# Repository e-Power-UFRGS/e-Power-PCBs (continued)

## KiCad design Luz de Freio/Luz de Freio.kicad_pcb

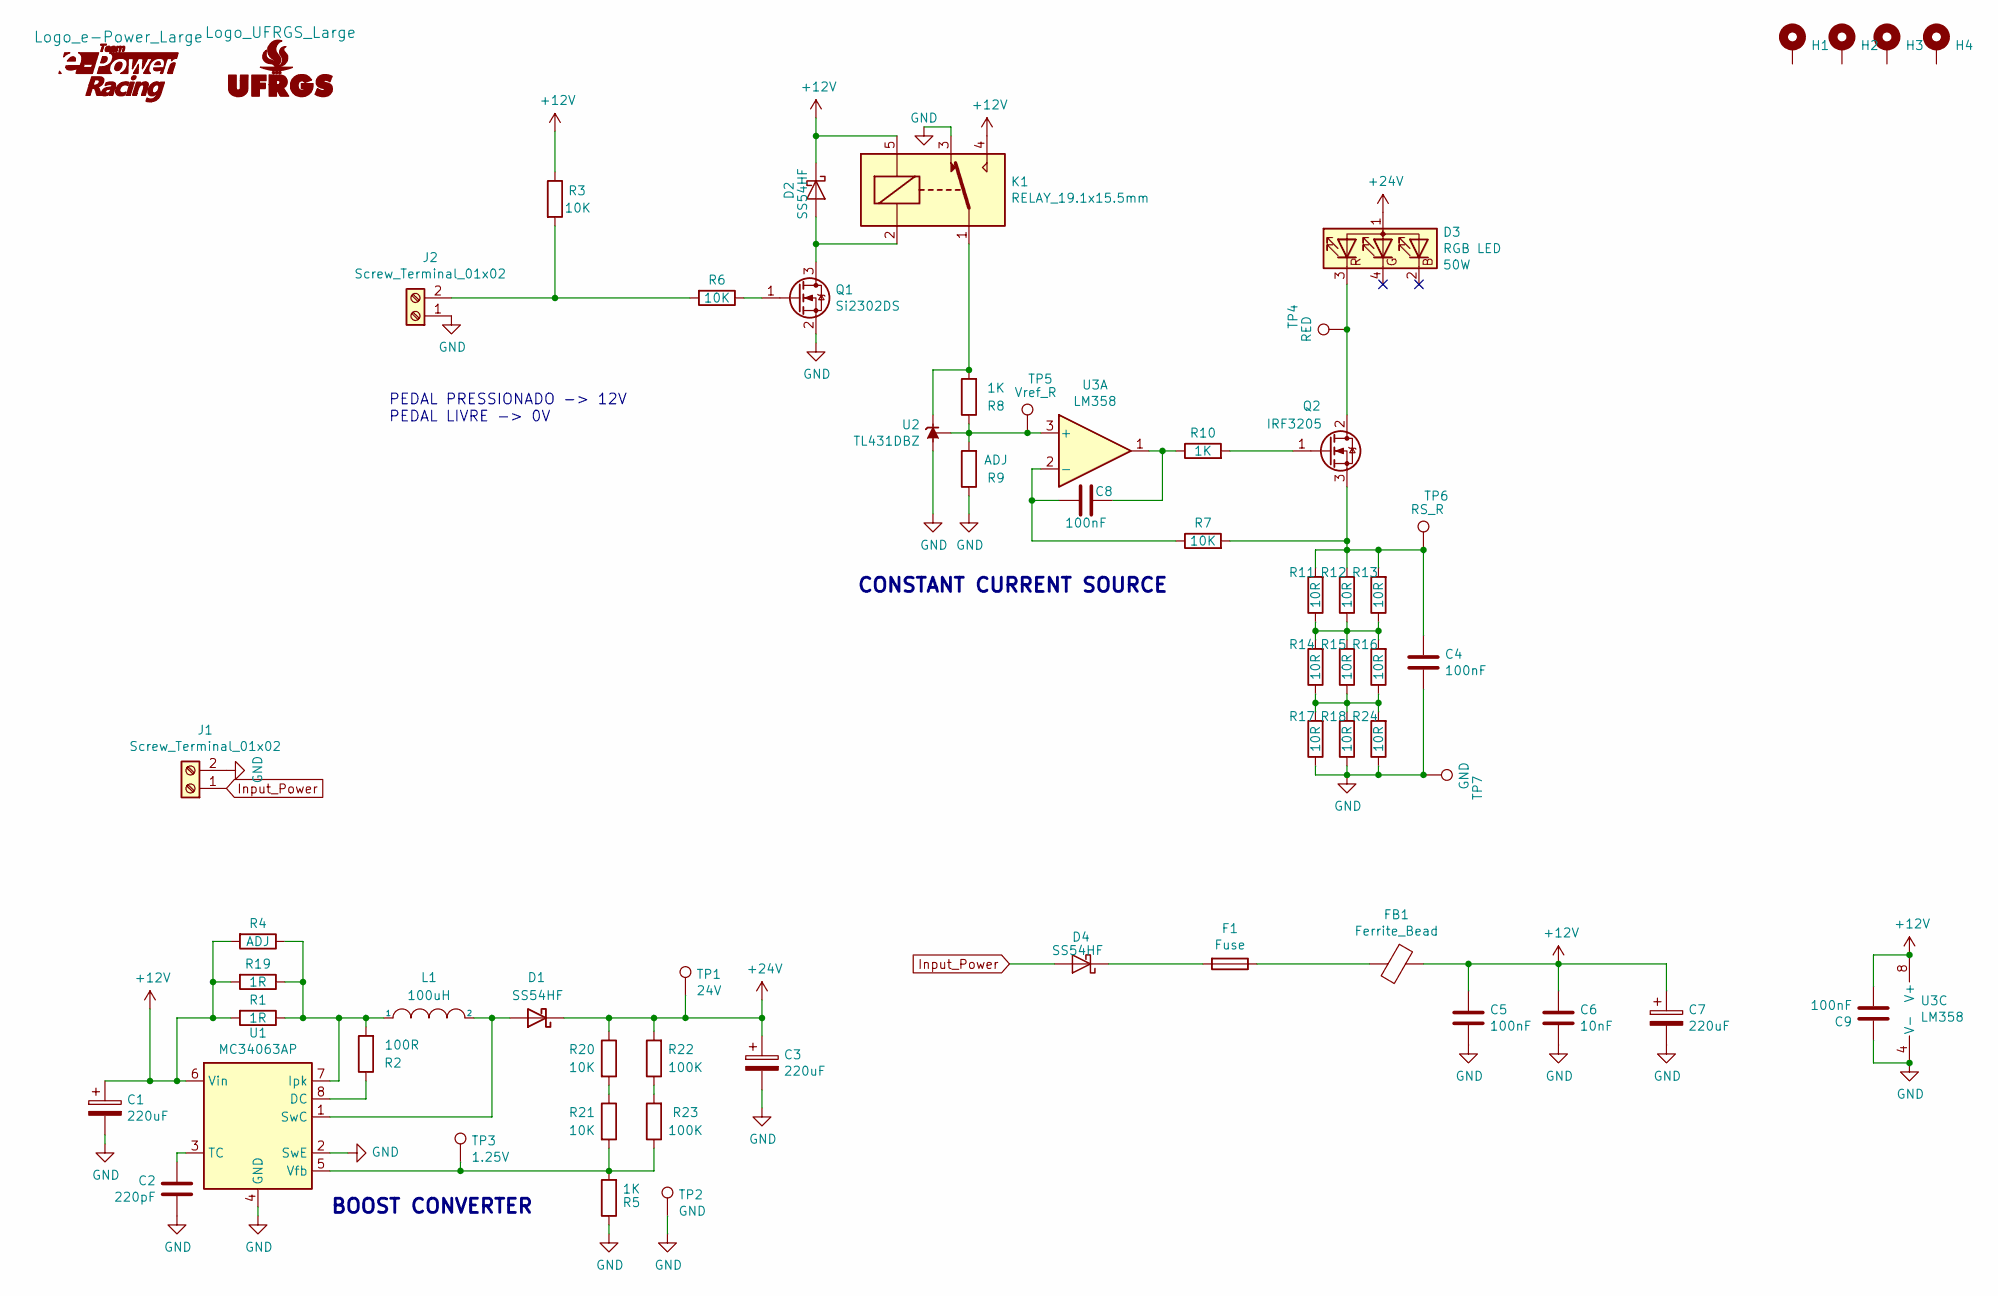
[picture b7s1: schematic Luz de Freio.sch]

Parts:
C1, C3: 220uF; CP_Elec_10x10; Voltage 16V
C2: 220pF; C_0805_2012Metric_Pad1.15x1.40mm_HandSolder
C4, C5, C9: 100nF; C_0805_2012Metric_Pad1.15x1.40mm_HandSolder
C6: 10nF; C_0805_2012Metric_Pad1.15x1.40mm_HandSolder
C7: 220uF; CP_Elec_10x10
C8: 100nF; C_0805_2012Metric
D1, D2, D4: SS54HF; DO-214AC
D3: RGB LED; TerminalBlock_Phoenix_MKDS-1,5-2_1x02_P5.08mm_Horizontal
F1: Fuse; FUSE_1206_3216Metric
FB1: Ferrite_Bead; FB_0805_2012Metric
G1: Logo_UFRGS_Large; Logo_UFRGS_14.7x8.0mm_SilkS
G2: Logo_e-Power_Large; Logo_e-Power_16.5x8.0mm_SilkS
H1, H2, H3, H4: MountingHole_Pad; MountingHole_3.2mm_M3_Pad_Via
J1, J2: Screw_Terminal_01x02; TerminalBlock_Phoenix_MKDS-1,5-2_1x02_P5.08mm_Horizontal
K1: RELAY_19.1x15.5mm; Relay_SPDT_SANYOU_SRD
L1: 100uH; L_12x12mm_H6mm
Q1: Si2302DS; SOT-23
Q2: IRF3205; TO-220-3_Horizontal_TabDown
R1, R19: 1R; R_0805_2012Metric
R2: 100R; R_0805_2012Metric
R3, R6, R7: 10K; R_0805_2012Metric_Pad1.15x1.40mm_HandSolder
R4: ADJ; R_0805_2012Metric
R5: 1K; R_0805_2012Metric
R8, R10: 1K; R_0805_2012Metric_Pad1.15x1.40mm_HandSolder
R9: ADJ; R_0805_2012Metric_Pad1.15x1.40mm_HandSolder
R11, R12, R13, R14, R15, R16, R17, R18, R24: 10R; R_0805_2012Metric_Pad1.15x1.40mm_HandSolder
R20, R21: 10K; R_0805_2012Metric
R22, R23: 100K; R_0805_2012Metric
TP1: 24V; TestPoint_Pad_D1.0mm
TP2, TP7: GND; TestPoint_Pad_D1.0mm
TP3: 1.25V; TestPoint_Pad_D1.0mm
TP4: RED; TestPoint_Pad_D1.0mm
TP5: Vref_R; TestPoint_Pad_D1.0mm
TP6: RS_R; TestPoint_Pad_D1.0mm
U1: MC34063AP; SOIC-8_3.9x4.9mm_P1.27mm
U2: TL431DBZ; SOT-23
U3: LM358; SOIC-8_3.9x4.9mm_P1.27mm

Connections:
+12V: C1.1, C5.1, C6.1, C7.1, C9.1, D2.1 (K), FB1.1, K1.4, K1.5, R1.2, R3.1, R4.2, R19.2, U1.6 (Vin), U3.8 (V+)
+24V: C3.1, D1.1 (K), D3.1 (A), R20.1, R22.2, TP1.1
GND: C1.2, C2.1, C3.2, C4.1, C5.2, C6.2, C7.2, C9.2, J1.2, J2.1, K1.3, Q1.2 (S), R5.1, R9.1, R17.1, R18.1, R24.1, TP2.1, TP7.1, U1.2 (SwE), U1.4 (GND), U2.3 (A), U3.4 (V-)
Input_Power: D4.2 (A), J1.1
unnamed: C2.2, U1.3 (TC)
unnamed: C4.2, Q2.3 (S), R7.2, R11.2, R12.2, R13.2, TP6.1
unnamed: C8.1, R10.1, U3.1
unnamed: C8.2, R7.1, U3.2 (-)
unnamed: D1.2 (A), L1.2, U1.1 (SwC)
unnamed: D2.2 (A), K1.2, Q1.3 (D)
unnamed: D3.3 (RK), Q2.2 (D), TP4.1
unnamed: D4.1 (K), F1.2
unnamed: F1.1, FB1.2
unnamed: J2.2, R3.2, R6.2
unnamed: K1.1, R8.2, U2.1 (K)
unnamed: L1.1, R1.1, R2.2, R4.1, R19.1, U1.7 (Ipk)
unnamed: Q1.1 (G), R6.1
unnamed: Q2.1 (G), R10.2
unnamed: R2.1, U1.8 (DC)
unnamed: R8.1, R9.2, TP5.1, U2.2 (REF), U3.3 (+)
unnamed: R11.1, R12.1, R13.1, R14.2, R15.2, R16.2
unnamed: R14.1, R15.1, R16.1, R17.2, R18.2, R24.2
unnamed: R20.2, R21.1
unnamed: R5.2, R21.2, R23.1, TP3.1, U1.5 (Vfb)
unnamed: R22.1, R23.2

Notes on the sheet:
CONSTANT CURRENT SOURCE
BOOST CONVERTER
PEDAL PRESSIONADO -> 12V PEDAL LIVRE -> 0V

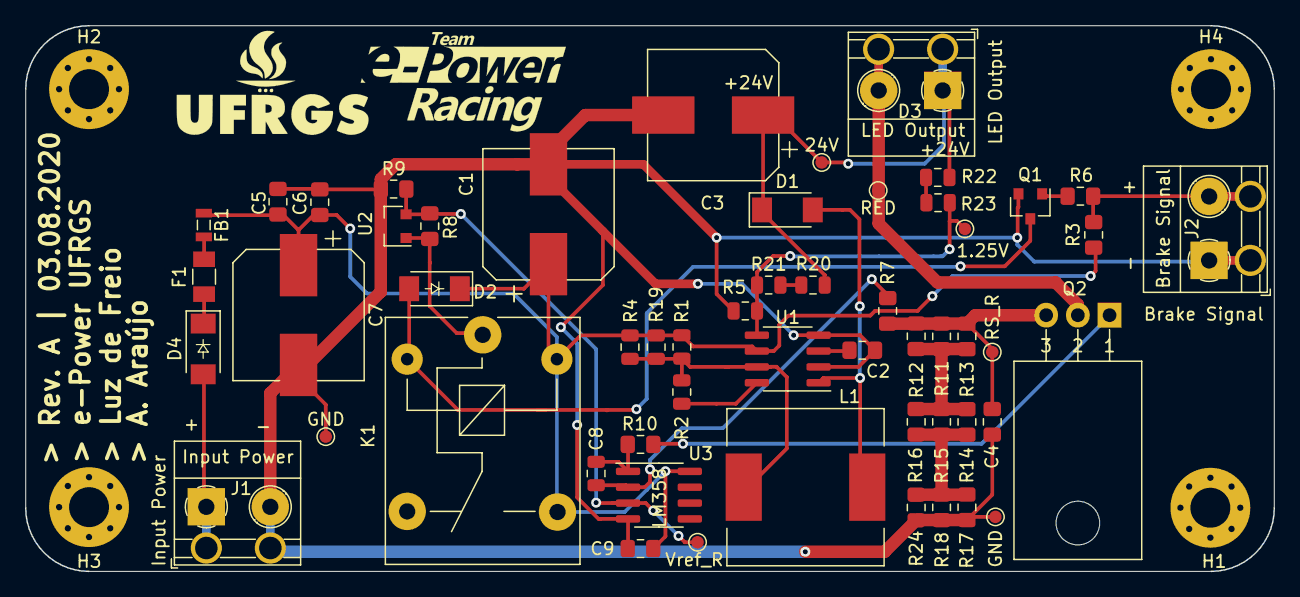
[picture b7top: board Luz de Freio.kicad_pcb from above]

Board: 2 copper layers, 100.1 x 43.7 mm, 61 parts (0 on the bottom side), 25 nets.

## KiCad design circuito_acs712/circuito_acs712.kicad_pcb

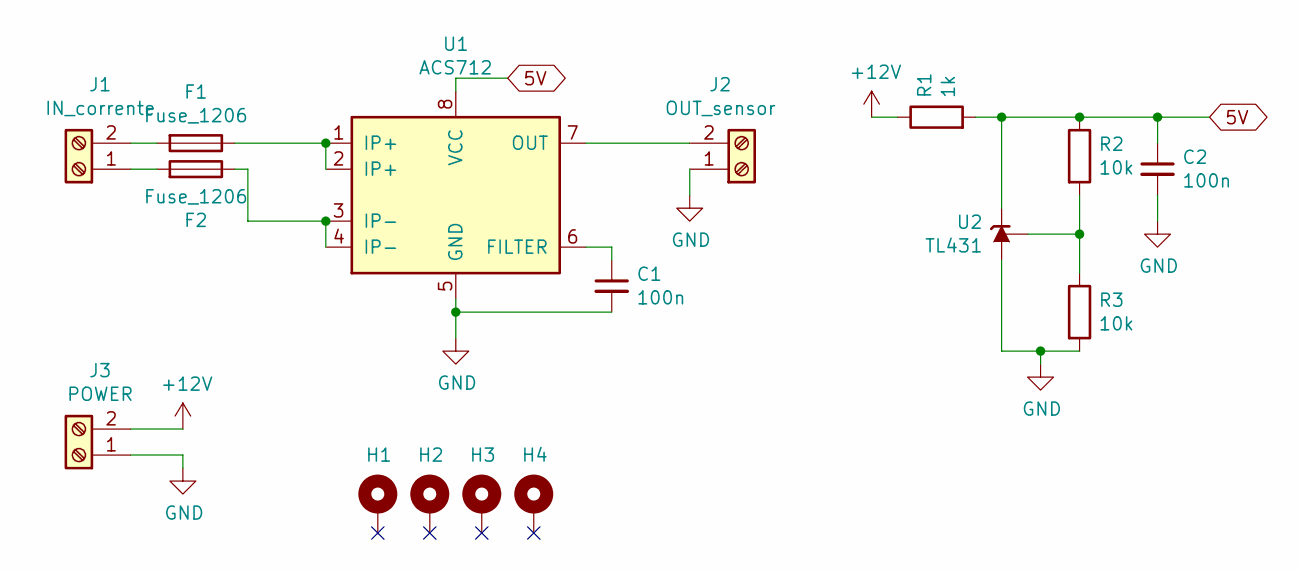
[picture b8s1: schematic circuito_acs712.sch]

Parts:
C1, C2: 100n; C_0805_2012Metric
F1, F2: Fuse_1206; FUSE_1206_3216Metric
H1, H2, H3, H4: MountingHole_Pad; MountingHole_3.2mm_M3_Pad_Via
J1: IN_corrente; TerminalBlock_Phoenix_MKDS-1,5-2_1x02_P5.08mm_Horizontal
J2: OUT_sensor; TerminalBlock_Phoenix_MKDS-1,5-2_1x02_P5.08mm_Horizontal
J3: POWER; TerminalBlock_Phoenix_MKDS-1,5-2_1x02_P5.08mm_Horizontal
R1: 1k; R_0805_2012Metric
R2, R3: 10k; R_0805_2012Metric
U1: ACS712; SOIC-8_3.9x4.9mm_P1.27mm
U2: TL431; SOT-23

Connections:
5V: C2.1, R1.2, R2.1, U1.8 (VCC), U2.2 (K)
+12V: J3.2, R1.1
GND: C1.2, C2.2, J2.1, J3.1, R3.2, U1.5 (GND), U2.3 (A)
unnamed: C1.1, U1.6 (FILTER)
unnamed: F1.1, U1.1 (IP+), U1.2 (IP+)
unnamed: F1.2, J1.2
unnamed: F2.1, U1.3 (IP-), U1.4 (IP-)
unnamed: F2.2, J1.1
unnamed: J2.2, U1.7 (OUT)
unnamed: R2.2, R3.1, U2.1 (REF)

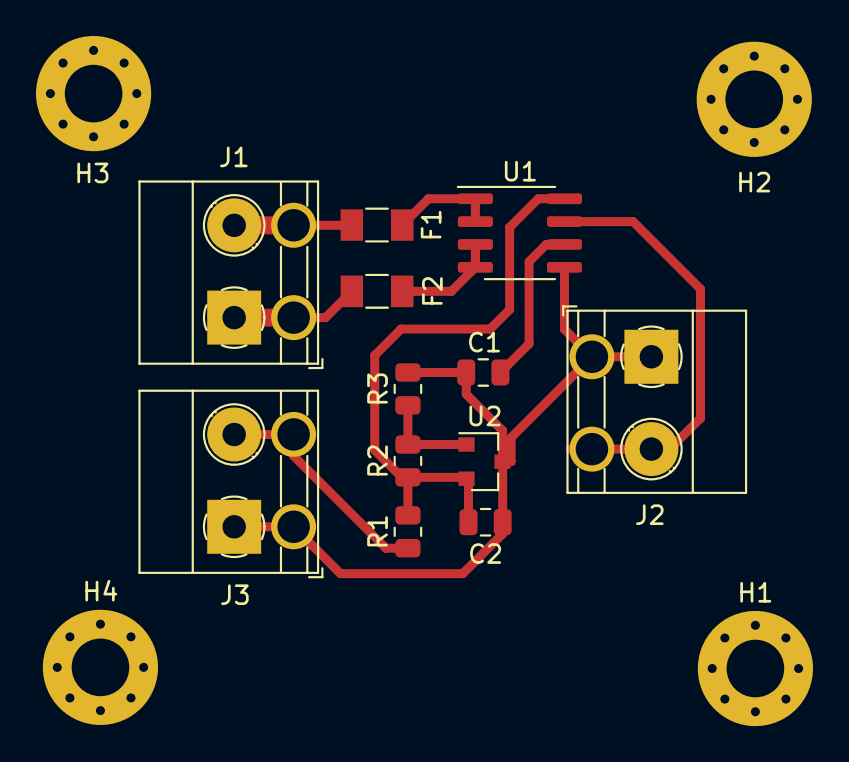
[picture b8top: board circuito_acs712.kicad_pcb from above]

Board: 2 copper layers, 16 parts (0 on the bottom side), 10 nets.

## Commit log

2020-07-19 adicionei a pasta do BMS ao repositorio
2020-07-19 add current sense block to the schematic
2020-07-21 changes made to the bms20s circuit
2020-07-21 adicionar o circuito do TSAL ao GIT
2020-07-22 add e-Power_conventions file
2020-07-22 added other PCB projects to git repository
2020-07-23 added rounded corners to conventions
2020-07-23 rounded corners
2020-07-23 updated ufrgs-pill
2020-08-01 update balancing circuit
2020-08-01 correctly positioned voltage sensors and balancing
2020-08-01 advances have been made on the voltage sensors
2020-08-03 updated have been made on currents and voltage sensors
2020-08-03 TSAL rounded corners
2020-08-03 Luz de Freio padrao e-power
2020-08-04 updates made on BMS
2020-08-05 Modified SET/RESET circuit. Added BSPD and AIL circuit.
2020-08-07 update all circuits
2020-08-07 add LM235_BRD to git
2020-08-07 update tsal
2020-08-07 review das placas
2020-08-07 review
2020-08-07 Diferencial Update
2020-08-10 schematic update BSPD and new layout not finishet
2020-08-11 AIL schematic and layout att. BSPD layout att.
2020-08-13 add 3d-renders images
2020-08-13 TSAL temp management update
2020-08-14 Revert "AIL schematic and layout att. BSPD layout att."
    This reverts commit 7e7712d535c298d88471c8cf66961c9a5b232e43.
2020-08-14 backups
2020-08-14 get BSPD
2020-08-14 recover BSPD
2020-08-14 update bms pcb
2020-08-15 update BMS
2020-08-15 Diferencial Layout Update/Main ECU Eeschema
2020-08-15 melhorias feitas no BMS
2020-08-16 Diferencial Layout Update
2020-08-18 Rev. B - BSPD and Rev. B - Set/Reset
2020-08-23 atualizacao esquematico
2020-08-24 Layout Main ECU and Layout Luz de Freio
2020-08-25 update all
2020-08-27 updates made on bms, almost done
2020-08-29 jlcpcb smt mounting pos file for BMS is update
2020-08-30 Fixed Schematic and Layout
2020-08-30 BSPD att.
2020-08-31 Update Layouyt
2020-09-01 backup AIL
2020-09-06 Set/Reset Rev. C
2020-09-07 Layout Fixes and CAN Connector Added
2020-09-07 att set/reset and ail 07/09/2020
2020-09-13 Changed Tracks Width
2020-09-17 Added CAN connectors / Fixes
2020-09-18 update pcbs
2020-09-18 generate gerbers for AIL
2020-09-18 geretate BSPD gerbers
2020-09-18 generate diferencial gerbers
2020-09-18 generate gerbers for brake light
2020-09-18 generate gerbers and add powertrain pcbs
2020-09-25 powertrain pcbs
2020-09-28 dimenssion AIL
2020-10-10 update shutdown
2020-11-02 create panel files
2020-11-06 add small option panel board
2020-12-22 circuito sensor de corrente
2021-01-20 placa fdcan
2021-03-04 esqueatico circuito BMS para monitoramento de temperatura
2021-03-04 att. bms temp
2021-03-08 layout att.1
2021-03-11 layout att 2
2021-03-14 layout att 3
2021-03-16 layout bms temp pronto
2021-03-19 layout final bms temp
2021-07-08 PCB tensao FT
2021-07-27 Add files via upload
    Divisor de tensão
2021-08-05 Placa BMS-temperatura
2021-09-21 BSPD atualizado e charger shutdown adicionado
2021-09-22 charger atualizacao
2021-09-22 simulation chargar shtdown circuit
2021-09-25 AIL atualizado
